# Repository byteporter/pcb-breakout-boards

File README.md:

# pcb-breakout-boards
Collection of simple PCBs I use for prototyping

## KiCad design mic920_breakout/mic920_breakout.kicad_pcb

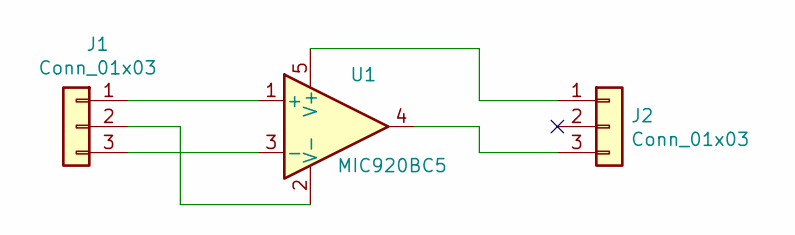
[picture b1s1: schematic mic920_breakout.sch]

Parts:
J1, J2: Conn_01x03; PinHeader_1x03_P2.54mm_Vertical
U1: MIC920BC5; SOT-353_SC-70-5_Handsoldering

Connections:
unnamed: J1.1, U1.1 (+)
unnamed: J1.2, U1.2 (V-)
unnamed: J1.3, U1.3 (-)
unnamed: J2.1, U1.5 (V+)
unnamed: J2.3, U1.4

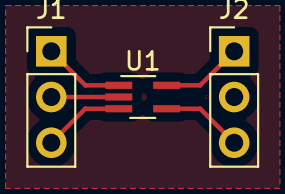
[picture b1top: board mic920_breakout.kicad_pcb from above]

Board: 2 copper layers, 3 parts (0 on the bottom side), 5 nets.

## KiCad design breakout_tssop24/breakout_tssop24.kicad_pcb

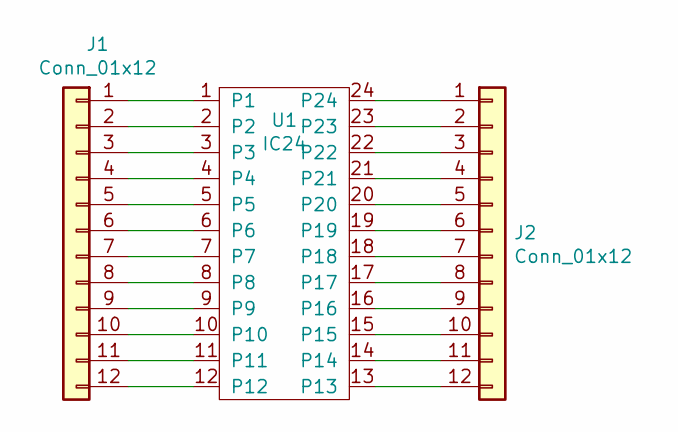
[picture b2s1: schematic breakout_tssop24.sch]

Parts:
J1, J2: Conn_01x12; SIP-12
U1: IC24; SOIC-24

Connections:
unnamed: J1.1, U1.1
unnamed: J1.2, U1.2
unnamed: J1.3, U1.3
unnamed: J1.4, U1.4
unnamed: J1.5, U1.5
unnamed: J1.6, U1.6
unnamed: J1.7, U1.7
unnamed: J1.8, U1.8
unnamed: J1.9, U1.9
unnamed: J1.10, U1.10
unnamed: J1.11, U1.11
unnamed: J1.12, U1.12
unnamed: J2.1, U1.24
unnamed: J2.2, U1.23
unnamed: J2.3, U1.22
unnamed: J2.4, U1.21
unnamed: J2.5, U1.20
unnamed: J2.6, U1.19
unnamed: J2.7, U1.18
unnamed: J2.8, U1.17
unnamed: J2.9, U1.16
unnamed: J2.10, U1.15
unnamed: J2.11, U1.14
unnamed: J2.12, U1.13

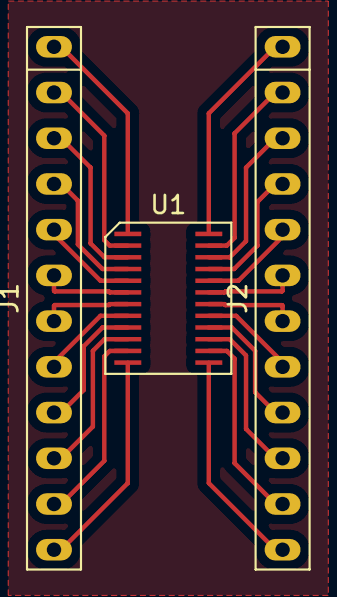
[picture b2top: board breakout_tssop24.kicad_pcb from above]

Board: 2 copper layers, 3 parts (0 on the bottom side), 24 nets.

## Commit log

2019-08-28 Added some pcb projects
2019-09-21 Added and updated boards
